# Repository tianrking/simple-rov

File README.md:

<div align="center">

# SimpleROV

**A compact four-thruster underwater robot.**

Printable mechanics · Documented assembly · MuJoCo simulation

[**English**](README.md) · [Español](README.es.md) · [简体中文](README.zh-CN.md)

**213 × 210 × 148 mm** &nbsp; · &nbsp; **4 thrusters** &nbsp; · &nbsp; **10 printed parts**

[Assembly guide](docs/assembly.md) · [Download](https://github.com/tianrking/simple-rov/releases) · [CAD files](mechanical/README.md) · [Simulation](docs/simulation.md) · [Gallery](docs/gallery.md)

</div>

SimpleROV brings the frame, thruster mounts, camera carrier, enclosure mounts and simulation into one reproducible project. Start with a mechanical fit check, then develop tethered remote control, depth hold and heading hold around the same coordinate system.

The **standard assembly has no top buoyancy foam or retention straps**. Mounting routes remain available for an optional buoyancy module, selected after measuring the completed vehicle's mass and trim. These images are CAD renderings, not photographs of tested hardware.

## Simulation videos

**Watch the 48-second overview directly below:** four actual MuJoCo scenarios, 720p H.264, live telemetry and the forward camera.

https://github.com/user-attachments/assets/2bf94293-84e5-456a-9249-f08cb007cc9f

| Chapter | Overview time | What to watch | Individual video |
|---|---|---|---|
| Basic motion | 00:00-00:12 | Rise, descend, move forward and turn | [Pool](docs/assets/videos/pool.mp4) |
| Water current | 00:12-00:24 | Current arrow, changing position and lateral drift | [Cross-current](docs/assets/videos/cross-current.mp4) |
| Tether load | 00:24-00:36 | Tension/slack state and line force at the chassis eye | [Tether](docs/assets/videos/tethered.mp4) |
| Motor failure | 00:36-00:48 | H_LEFT at zero thrust, rank loss and allocation residual | [Motor fault](docs/assets/videos/motor-fault.mp4) |

[All video players and reproduction details](docs/videos.md) · [Download the overview MP4](docs/assets/videos/simple-rov-overview.mp4)

<details>
<summary><strong>Animated preview for mirrors without native video playback</strong></summary>

</details>

These are simulated trajectories with uncalibrated parameters, sensor feedback and seed 0. They are classical-control demonstrations, not physical robot footage. MP4 originals, per-frame state traces and exact run metadata are committed alongside the rendering source.

## At a glance

| Mechanics | Propulsion | Development |
|---|---|---|
| Compact load-bearing frame | Two horizontal + two vertical thrusters | Editable CadQuery source and STEP |
| Commercial central dry enclosure | Forward/reverse, ascent/descent, yaw | Independent, bed-oriented STL files |
| Removable fairing and skids | Differential vertical thrust assists roll | MuJoCo environment and classical control |
| Optional top buoyancy module | Four independent force commands | Illustrated assembly, BOM and checks |

| Specification | Current reference |
|---|---|
| Standard envelope, L × W × H | **213 × 210 × 148 mm** |
| With the reference buoyancy module | 213 × 210 × 184.7 mm |
| Main printed parts | 10, plus 2 separate motor-fit coupons |
| Thruster reference | 4 × APISQUEEN X2 complete waterproof thrusters |
| Central enclosure reference | Blue Robotics 50 mm series, 150 mm tube, 58 mm outside diameter |
| Camera reference | Blue Robotics Low-Light HD USB Camera |
| Coordinates | X forward, Y left, Z up; CAD in mm, simulation in m |

Dimensions exclude the final cables, penetrators, tether termination, strap buckles and ballast. Sway and pitch have no independent actuators. Actual motor threads, cable exits and the complete electrical packaging still need physical confirmation.

## Explore the structure

| Inside the frame | Optional buoyancy module |
|:---:|:---:|
|  |  |

The interior view removes the fairing and pressure enclosure components to show the camera carrier, tray and mounts. It does not imply that the final battery, controller, four ESCs and video host have been packaged.

<details>
<summary><strong>Open the six individual views</strong></summary>

| Front | Rear |
|:---:|:---:|
|  |  |

| Left | Right |
|:---:|:---:|
|  |  |

| Top | Bottom |
|:---:|:---:|
|  |  |

</details>

### In Onshape

These are **actual screenshots of the historical cloud assembly**, shown with the optional foam and straps fitted. The repository's standard STEP remains the reference for the default, foam-free configuration.

| Assembly workspace | Profile detail |
|:---:|:---:|
|  |  |

[Open the public Onshape assembly](https://cad.onshape.com/documents/256f9be06adfdc472f7aac06/w/aefb43ce726d3d5c24877f23/e/1186baa4f5bb2c01f6be971a) · [View provenance and import limitations](docs/gallery.md#onshape-screenshots)

## What each part does

| Part | Qty. | Purpose |
|---|---:|---|
| Load chassis | 1 | Carries thrust loads and joins the skids, enclosure, mounts and fairing; provides tether and ballast interfaces |
| Upper fairing | 1 | Protects the structure and defines its outline; freely floods and is not a pressure vessel |
| Skids | 2 | Support the vehicle on a bench or pool floor and protect its underside |
| Enclosure clamps | 2 | Retain the commercial tube with soft liners; do not seal the endcaps |
| Vertical carriers | 2 | Mount the vertical thrusters and transfer their loads to the chassis |
| Internal tray | 1 | Supports the camera carrier and future electronics adapters; positive axial retention remains to be designed |
| Camera carrier | 1 | Positions the camera board and provides lens, USB and fastener clearance |
| Commercial pressure enclosure | 1 set | Keeps ordinary electronics dry when correctly assembled and leak-tested |
| Commercial thrusters | 4 | Complete motor, propeller and duct assemblies; not printed by this project |
| Buoyancy foam and straps | Optional | Add buoyancy and adjust trim after measurement |

## Choose an assembly

| Configuration | Top foam / straps | Assembly STEP | With nominal metal fasteners |
|---|---|---|---|
| **Standard** `base` | None | [simple-rov.step](mechanical/assemblies/simple-rov.step) | [Fastener assembly](mechanical/assemblies/simple-rov-with-fasteners.step) |
| Optional `with-buoyancy` | 2 foam pieces / 4 straps | [Buoyancy assembly](mechanical/assemblies/simple-rov-with-buoyancy.step) | [Buoyancy + fasteners](mechanical/assemblies/simple-rov-buoyancy-with-fasteners.step) |

Both configurations share the same ten printed parts. Foam is cut from suitable closed-cell material; it is **not printed as part of the fairing**. Its default purchase quantity is zero, with optional quantities recorded separately.

Omitting foam does not establish positive buoyancy or guarantee a passive ascent. Weigh the complete vehicle, measure displacement and check fully submerged trim before deciding whether to add foam or ballast. See [buoyancy and trim](docs/buoyancy.md).

## Build a first prototype

1. **Check one motor first.** Buy one reference thruster and a matching bidirectional ESC. Test both [fit coupons](mechanical/fit_coupons/) against the actual mounting face, holes, blind depth and cable exit.
2. **Check the dry payload.** Lay out the real battery, four ESCs, controller, video host, connectors and wiring at full scale before assuming they fit the tube.
3. **Print and assemble.** Use the [print manifest](bom/PRINT_MANIFEST.csv), [fastener BOM](bom/BOM_FASTENERS.csv) and [illustrated guide](docs/assembly.md). Install skids before horizontal thrusters obstruct their tool paths.
4. **Complete retention and wiring.** Add board-specific insulated adapters and positive tray retention. Select penetrators for the actual cable construction.
5. **Leak-test and trim.** Test the complete empty enclosure, then use representative payload mass to establish buoyancy and balance.
6. **Run controlled shallow-water checks.** Verify individual thrust directions, remote commands, depth/heading hold and loss-of-command shutdown in a recoverable setting.

The guide specifies screw directions, washers, quantities and inspection hold points. Start with [assembly](docs/assembly.md), [acceptance](docs/acceptance.md) and the [prototype build plan](docs/build-plan.md).

## Run the simulation

From the repository root, using Python 3.12:

```bash
git clone https://github.com/tianrking/simple-rov.git
cd simple-rov
python3 -m venv .venv
source .venv/bin/activate
python -m pip install -r requirements/sim.txt
python simulation/mujoco/run.py --viewer --manual --seconds 300
```

On Windows, activate with `.venv\Scripts\activate`. On macOS, after installing dependencies, you can also open `launch-macos.command`.

| Control | Input |
|---|---|
| Forward / reverse | Hold W / S; release to cancel surge thrust |
| Turn left / right | A / D; change heading target by 15° |
| Ascend / descend | U / J; change depth target by 0.1 m |
| Hold current depth and heading | X; does not lock horizontal position |
| Orbit / zoom | Left mouse drag / scroll wheel |
| Quit | Esc or close the window |

The dedicated driving window isolates these keys from MuJoCo's built-in viewer shortcuts. Losing focus cancels surge thrust; the vehicle can still coast.

```bash
# Display the optional assembly
python simulation/mujoco/run.py --viewer --manual --configuration with-buoyancy --seconds 300

# Record an automatic demonstration, state CSV and camera views
python simulation/mujoco/run.py --render --output-dir runs/demo
```

### Physics and control

Powered by **MuJoCo 4.0.1**, the foundation includes relative-current drag, buoyancy, delayed/rate-limited actuators, bounded allocation, sensor proxies, classical control, a lumped tether and fault scenarios. [Simulation foundation](docs/simulation-foundation.md). **Mass, inertia, centers of gravity/buoyancy, displacement, drag and reverse thrust are uncalibrated example parameters.** Changing the assembly changes visuals and associated collision proxies; it does not automatically recalculate those parameters.

This is a fully submerged, still-water model. It includes configurable current and a tension-only tether approximation; it does not include waves, free-surface transitions, distributed cable dynamics, CFD or realistic underwater optics. Open it through `run.py`: loading an XML alone omits the Python underwater forces.

```python
from simulation.mujoco.environment import ROV

rov = ROV(configuration="base")
for _ in range(1000):
    forces = rov.controller(depth=1.2, surge_N=2.0, yaw=0.0)
    position, attitude, velocity, angular_velocity = rov.step(forces)
```

Commands are forces in newtons, ordered horizontal-left, horizontal-right, vertical-left, vertical-right. They are not PWM or RPM. Keyboard commands set surge thrust, target depth and target heading; classical feedback stabilizes depth, roll and heading. [Driving and control documentation](docs/simulation.md).

To try a water current while driving:

```bash
python simulation/mujoco/run.py --scenario cross-current --viewer --manual --seconds 300
```

The development path is **mechanical fit and assembly → tethered remote operation → classical stabilization → measured calibration and shallow-water trials**. Custom PCB work is deferred; the current release focuses on mechanics, assembly and remote-control simulation.

## Edit and reproduce

| Need | Entry point |
|---|---|
| Ten bed-oriented prints | [mechanical/stl/](mechanical/stl/) |
| Ten editable STEP parts | [mechanical/step_parts/](mechanical/step_parts/) |
| Dimensions and CAD source | [parameters.json](mechanical/parameters.json) · [build.py](mechanical/build.py) |
| Configuration inventory | [configurations.json](mechanical/configurations.json) |
| Printed, purchased and metal parts | [bom/](bom/) |
| Installation instructions | [Assembly guide](docs/assembly.md) · [PDF](docs/assembly.pdf) |
| Change workflow and checks | [Development guide](docs/development.md) |

<details>
<summary><strong>CAD and simulation rebuild commands</strong></summary>

```bash
python -m pip install -r requirements/cad.txt
python mechanical/build.py
python mechanical/build_fit_coupons.py
python mechanical/verify.py
python mechanical/export_metadata.py
python mechanical/verify_configurations.py
python simulation/mujoco/build_model.py
python simulation/mujoco/verify.py
python simulation/mujoco/verify_manual.py
```

</details>

When changing motors, check the full envelope, mounting-face offset, hole pattern, depth, cable exit, propeller flow paths and screw length. Keep CAD, BOM, documents and simulation in sync. Existing part IDs are retained for compatibility with printed parts and hole tables.

```text
mechanical/          Parametric CAD, separate parts, assemblies and supplier references
simulation/mujoco/   Underwater forces, classical control, driving and checks
bom/                 Print, purchase, fastener and interface records
electronics/         Future KiCad work and mechanical interface constraints
firmware/            Future onboard implementation and failure handling
docs/                Assembly, design, trim, simulation, development and images
validation/          Digital check records and historical Onshape import records
requirements/        Dependencies grouped by purpose
runs/                Local outputs; excluded from version control
```

## Project status

| Available now | Still to validate or develop |
|---|---|
| Parametric mechanics, separate prints and two assembly variants | Actual motor mounting depth, cable exits and print load capacity |
| Illustrated guide, mechanical BOM and hole coordinates | Full electronics packaging, tray retention, penetrators and thermal management |
| MuJoCo demonstrator and classical control | Measured mass, trim, thrust and hydrodynamic calibration |
| Digital consistency and regression checks | Physical assembly, sealing and shallow-water trials |

PCB manufacturing files and flashable firmware are future work. Digital checks are evidence about files, geometry and software, not a reliability or depth certification. [Status](STATUS.json) · [Roadmap](docs/roadmap.md) · [Changelog](CHANGELOG.md).

## Rights and sources

This repository is public for review. **All rights reserved for original content; no open-source license is granted.** Third-party CAD, manufacturer drawings and dependencies retain their owners' rights. [License](LICENSE) · [Third-party notices](THIRD_PARTY_NOTICES.md) · [Sources](SOURCES.json).

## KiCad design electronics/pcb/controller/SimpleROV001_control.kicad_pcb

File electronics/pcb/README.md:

# SimpleROV v0.0.1 hardware

Frozen engineering controller PCB for the current80x32mm interface. Native KiCad10 sources, checked reports, procurement/assembly files and mechanical exports are provided. This is a prototype design ready for independent fabrication review, not a tested propulsion system.

- Open controller/SimpleROV001_control.kicad_pro. Its local symbol library, used standard footprint subsets, modified footprint library and STEP models are included.
- verification/ERC.json and DRC.json are untouched KiCad CLI reports. DRC has0violations/0unconnected/0schematic-parity issues with no ignored DRC checks or exclusions. ERC has0violations; only SPICE model checking is ignored, because no SPICE simulation is claimed.
- controller/source/netlist.xml is exported from the final schematic. docs/CONNECTOR_PINOUT.csv and controller/source/physical_placement.json follow the final native PCB, not the earlier proposal.
- controller/BOM.csv lists individual purchased parts; controller/manufacturing holds fabrication layers, separate drills and SMT-only placement data. USB is a manual mixed-technology placement.
- mechanical/controller_assembled.step uses board-bottom origin and includes111 KiCad model instances plus explicit IMU/USB envelopes. Mated connector keepouts and wire-bend reservations are separate STEP files, built from final native placement. Apply world translation[-50,-16,13]mm to each. Complete enclosure and cable fit is still a system integration task.
- docs/FAULT_CHAIN_AND_SENSE.md gives J9 arming behavior, non-inverting PWM and the1k0.5W source-resistor MPN/formula. docs/DESIGN_AND_QUALIFICATION.md specifies assembly and the unperformed physical qualification stages.
- controller/source/rebuild.py reproduces a separate candidate from frozen JSON, local libraries and the saved route session. It reruns ERC/DRC. See controller/source/REPRODUCE.md.

The prototype requires the exact5V-BEC ESC interface. Inhibit is static HIGH/no frames and does not prove the motor stops. First system commissioning is limited to regulated12V/5A total, per the main system plan. No board firmware or physical bench tests are represented as completed.

Original SimpleROV project materials:All rights reserved. Redistributed KiCad collections and modified KiCad footprints remain under the upstream CC BY-SA4.0 license with its electronic-design exception; see controller/third_party. No vendor datasheet full texts are redistributed. This package does not write, commit or push the shared repository.

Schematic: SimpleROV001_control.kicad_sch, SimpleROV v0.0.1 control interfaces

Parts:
C1, C2: 4.7u 10V; C_0805_2012Metric; MPN GRM21BR71A475KA73L
C3, C19, C21, C22, C23, C24, C25, C26, C27, C28, C29, C32: 100n 16V; C_0603_1608Metric; MPN GRM188R71C104KA01D
C4, C14: 1u 16V; C_0603_1608Metric; MPN GRM188R71C105KA12D
C5, C18: 2.2u 10V; C_0603_1608Metric; MPN GRM188R71A225KE15D
C6, C7, C8, C9, C10, C11, C12, C13, C15: 100n 16V; C_0402_1005Metric; MPN GRM155R71C104KA88D
C16, C17: 15p 50V C0G; C_0603_1608Metric; MPN GRM1885C1H150JA01D
C20, C30, C31: 10n 50V; C_0603_1608Metric; MPN GRM188R71H103KA01D
D1: SS14; D_SMA; MPN SS14-E3/61T
D2: SS14; D_SMA_SilkTrim; MPN SS14-E3/61T
D3: USBLC6-2SC6; SOT-23-6; MPN USBLC6-2SC6
D4: BAT54S,215; SOT-23; MPN BAT54S,215
D5: STATUS GREEN; LED_0603_1608Metric; MPN LTST-C190KGKT
F1: 500mA 32V FAST; Fuse_1206_3216Metric; MPN 0467.500NR
J1: J1 SYS5V / GND; JST_GH_BM02B-GHS-TBT_1x02-1MP_P1.25mm_Vertical; MPN BM02B-GHS-TBT(LF)(SN)
J2: J2 GND / UART_TX_PORT / UART_RX_PORT; JST_GH_BM03B-GHS-TBT_1x03-1MP_P1.25mm_Vertical; MPN BM03B-GHS-TBT(LF)(SN)
J3: J3 ESC_HL_5V / ESC_HL_PWM_PORT / ESC_HL_GND; JST_GH_BM03B-GHS-TBT_1x03-1MP_P1.25mm_Vertical; MPN BM03B-GHS-TBT(LF)(SN)
J4: J4 ESC_HR_5V / ESC_HR_PWM_PORT / ESC_HR_GND; JST_GH_BM03B-GHS-TBT_1x03-1MP_P1.25mm_Vertical; MPN BM03B-GHS-TBT(LF)(SN)
J5: J5 ESC_VL_5V / ESC_VL_PWM_PORT / ESC_VL_GND; JST_GH_BM03B-GHS-TBT_1x03-1MP_P1.25mm_Vertical; MPN BM03B-GHS-TBT(LF)(SN)
J6: J6 ESC_VR_5V / ESC_VR_PWM_PORT / ESC_VR_GND; JST_GH_BM03B-GHS-TBT_1x03-1MP_P1.25mm_Vertical; MPN BM03B-GHS-TBT(LF)(SN)
J7: J7 DEPTH_3V3 / DEPTH_SCL / DEPTH_SDA / GND; JST_GH_BM04B-GHS-TBT_1x04-1MP_P1.25mm_Vertical; MPN BM04B-GHS-TBT(LF)(SN)
J8: J8 LEAK_LIMIT / LEAK_RETURN; JST_GH_BM02B-GHS-TBT_1x02-1MP_P1.25mm_Vertical; MPN BM02B-GHS-TBT(LF)(SN)
J9: J9 V3V3 / ARM_KEY; JST_GH_BM02B-GHS-TBT_1x02-1MP_P1.25mm_Vertical; MPN BM02B-GHS-TBT(LF)(SN)
J10: BATTERY SENSE + ONLY; TestPoint_Pad_D2.0mm; MPN BATTERY SENSE + ONLY
J11: USB SERVICE ONLY; USB_MicroB_Molex105017_SilkTrim; MPN 1050170001
R1, R4, R9, R14, R44, R48: 1k; R_0603_1608Metric; MPN RC0603FR-071KL
R2, R34, R35: 33; R_0603_1608Metric; MPN RC0603FR-0733RL
R3, R5, R15, R26, R27, R28, R29, R45: 10k; R_0603_1608Metric; MPN RC0603FR-0710KL
R6, R7: 27; R_0603_1608Metric; MPN RC0603FR-0727RL
R8, R38: 10; R_0603_1608Metric; MPN RC0603FR-0710RL
R10, R12, R13, R16, R17, R22, R23, R24, R25, R39: 100k; R_0603_1608Metric; MPN RC0603FR-07100KL
R11: 2.2k; R_0603_1608Metric; MPN RC0603FR-072K2L
R18, R19, R20, R21: 365; R_0603_1608Metric; MPN RC0603FR-07365RL
R30, R31, R32, R33, R46, R47: 100; R_0603_1608Metric; MPN RC0603FR-07100RL
R36, R37: 4.7k; R_0603_1608Metric; MPN RC0603FR-074K7L
R40, R41: 3.3k; R_0603_1608Metric; MPN RC0603FR-073K3L
R42: 147k 0.1%; R_0603_1608Metric; MPN RT0603BRD07147KL
R43: 27k 0.1%; R_0603_1608Metric; MPN RT0603BRD0727KL
R49: 330; R_0603_1608Metric; MPN RC0603FR-07330RL
SW1: BOOTSEL; SW_SPST_B3U-1000P; MPN B3U-1000P
SW2: RESET; SW_SPST_B3U-1000P; MPN B3U-1000P
TP1: SWDIO; TestPoint_Pad_D1.0mm; MPN SWDIO
TP2: SWCLK; TestPoint_Pad_D1.0mm; MPN SWCLK
TP3: GND; TestPoint_Pad_D1.0mm; MPN GND
TP4: V3V3; TestPoint_Pad_D1.0mm; MPN V3V3
TP5: RUN; TestPoint_Pad_D1.0mm; MPN RUN
TP6: ARM_LATCH_Q; TestPoint_Pad_D1.0mm; MPN ARM_LATCH_Q
U1: RP2040; QFN-56-1EP_7x7mm_P0.4mm_EP3.2x3.2mm; MPN RP2040
U2: TLV75533PDBVR; SOT-23-5; MPN TLV75533PDBVR
U3: ICM-42688-P; LGA-14_3x2.5mm_P0.5mm_LayoutBorder3x4y; MPN ICM-42688-P
U4: W25Q16JVSNIQ; SOIC-8_3.9x4.9mm_P1.27mm; MPN W25Q16JVSNIQ
U5, U6, U7, U8: TLP2361(TPL,E; SO-5-6_4.55x3.7mm_P1.27mm; MPN TLP2361(TPL,E
U9: STWD100NXWY3F; SOT-23-5; MPN STWD100NXWY3F
U10: SN74LVC1G11DCKR; SOT-363_SC-70-6; MPN SN74LVC1G11DCKR
U11: SN74LVC126APWR; TSSOP-14_4.4x5mm_P0.65mm; MPN SN74LVC126APWR
U12: SN74HCS74PWR; TSSOP-14_4.4x5mm_P0.65mm; MPN SN74HCS74PWR
U13: SN74LVC1G97DCKR; SOT-363_SC-70-6; MPN SN74LVC1G97DCKR
Y1: 12MHz CL10p; Crystal_SMD_3225-4Pin_3.2x2.5mm; MPN ABM8-272-T3

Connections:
/ARM_CLEAR_DRIVE: R14.1, U13.4 (Y)
/ARM_CLR: R48.2, U12.1 (CLR1)
/ARM_CLR_RC: C21.1, R13.2, R14.2, R48.1
/ARM_FEED: J9.1 (3V3_ARM_FEED), R49.2
/ARM_KEY: J9.2 (ARM_KEY), R11.1, U1.15 (GPIO12), U10.1 (A), U13.6 (In2)
/ARM_LATCH_Q: TP6.1, U1.18 (GPIO15), U10.3 (B), U12.5 (Q1)
/ARM_SET: R12.1, U1.34 (GPIO22), U12.3 (CLK1)
/AVDD: C14.1, C15.1, R8.2, U1.43 (ADC_AVDD)
/BOOT_BTN: R4.2, SW1.1
/DEPTH_3V3: J7.1 (DEPTH_3V3), R38.2
/DEPTH_SCL: J7.2 (DEPTH_SCL), R34.2, R36.2
/DEPTH_SCL_MCU: R34.1, U1.7 (GPIO5)
/DEPTH_SDA: J7.3 (DEPTH_SDA), R35.2, R37.2
/DEPTH_SDA_MCU: R35.1, U1.6 (GPIO4)
/ESC_HL_5V: C26.1, J3.1 (ESC_HL_5V), U5.6 (VDD)
/ESC_HL_GND: C26.2, J3.3 (ESC_HL_GND), U5.4 (GND)
/ESC_HL_PWM: R30.1, U5.5 (VO)
/ESC_HL_PWM_PORT: J3.2 (ESC_HL_PWM_PORT), R30.2
/ESC_HR_5V: C27.1, J4.1 (ESC_HR_5V), U6.6 (VDD)
/ESC_HR_GND: C27.2, J4.3 (ESC_HR_GND), U6.4 (GND)
/ESC_HR_PWM: R31.1, U6.5 (VO)
/ESC_HR_PWM_PORT: J4.2 (ESC_HR_PWM_PORT), R31.2
/ESC_VL_5V: C28.1, J5.1 (ESC_VL_5V), U7.6 (VDD)
/ESC_VL_GND: C28.2, J5.3 (ESC_VL_GND), U7.4 (GND)
/ESC_VL_PWM: R32.1, U7.5 (VO)
/ESC_VL_PWM_PORT: J5.2 (ESC_VL_PWM_PORT), R32.2
/ESC_VR_5V: C29.1, J6.1 (ESC_VR_5V), U8.6 (VDD)
/ESC_VR_GND: C29.2, J6.3 (ESC_VR_GND), U8.4 (GND)
/ESC_VR_PWM: R33.1, U8.5 (VO)
/ESC_VR_PWM_PORT: J6.2 (ESC_VR_PWM_PORT), R33.2
/FLASH_CS: R3.2, R4.1, U1.56 (~QSPI_SS), U4.1 (CS)
/GND: C1.2, C2.2, C3.2, C4.2, C5.2, C6.2, C7.2, C8.2, C9.2, C10.2, C11.2, C12.2, C13.2, C14.2, C15.2, C16.2, C17.2, C18.2, C19.2, C20.2, C21.2, C22.2, C23.2, C24.2, C25.2, C30.2, C31.2, C32.2, D3.2 (GND), D4.1 (A1), D5.1 (K), J1.2 (GND), J2.1 (GND), J7.4 (GND), J11.5 (GND), J11.SH (SHIELD), R10.2, R11.2, R12.2, R13.1, R16.2, R17.2, R22.2, R23.2, R24.2, R25.2, R41.2, R43.2, R45.2, SW1.2, SW2.2, TP3.1, U1.19 (TESTEN), U1.57 (GND), U2.2 (GND), U3.2 (RESV), U3.3 (RESV), U3.6 (GND), U3.7 (RESV_GND), U3.9 (INT2_FSYNC), U3.10 (RESV), U3.11 (RESV), U4.4 (GND), U9.2 (GND), U9.3 (EN), U10.2 (GND), U11.7 (GND), U12.7 (GND), U12.11 (CLK2), U12.12 (D2), U12.13 (CLR2), U13.1 (In1), U13.2 (GND), Y1.2 (GND), Y1.4 (GND)
/IMU_CS: U1.28 (GPIO17), U3.12 (AP_CS)
/IMU_INT: U1.31 (GPIO20), U3.4 (INT1)
/IMU_MISO: U1.27 (GPIO16), U3.1 (AP_SDO)
/IMU_MOSI: U1.30 (GPIO19), U3.14 (AP_SDI)
/IMU_SCK: U1.29 (GPIO18), U3.13 (AP_SCLK)
/LEAK_ADC: C31.1, R39.2, R40.1, U1.39 (GPIO27/ADC1)
/LEAK_LIMIT: J8.1 (LEAK_LIMIT), R40.2
/LEAK_RETURN: J8.2 (LEAK_RETURN), R41.1
/LED_HL: R18.2, U5.1 (A)
/LED_HR: R19.2, U6.1 (A)
/LED_STATUS_A: D5.2 (A), R9.2
/LED_VL: R20.2, U7.1 (A)
/LED_VR: R21.2, U8.1 (A)
/MCU_ENABLE: R10.1, U1.14 (GPIO11), U10.6 (C)
/OUTPUT_ENABLE: R17.1, U10.4 (Y), U11.1 (OE1), U11.4 (OE2), U11.10 (OE3), U11.13 (OE4)
/PWM_HL_BUF: R26.1, U5.3 (K), U11.3 (Y1)
/PWM_HL_RAW: R22.1, U1.8 (GPIO6), U11.2 (A1)
/PWM_HR_BUF: R27.1, U6.3 (K), U11.6 (Y2)
/PWM_HR_RAW: R23.1, U1.9 (GPIO7), U11.5 (A2)
/PWM_VL_BUF: R28.1, U7.3 (K), U11.8 (Y3)
/PWM_VL_RAW: R24.1, U1.11 (GPIO8), U11.9 (A3)
/PWM_VR_BUF: R29.1, U8.3 (K), U11.11 (Y4)
/PWM_VR_RAW: R25.1, U1.12 (GPIO9), U11.12 (A4)
/QSPI_IO0: U1.53 (QSPI_SD0), U4.5 (DI_IO0)
/QSPI_IO1: U1.55 (QSPI_SD1), U4.2 (DO_IO1)
/QSPI_IO2: U1.54 (QSPI_SD2), U4.3 (WP_IO2)
/QSPI_IO3: U1.51 (QSPI_SD3), U4.7 (HOLD_IO3)
/QSPI_SCLK: R2.2, U4.6 (CLK)
/QSPI_SCLK_MCU: R2.1, U1.52 (QSPI_SCLK)
/RUN: R5.2, SW2.1, TP5.1, U1.26 (RUN)
/STATUS_LED: R9.1, U1.17 (GPIO14)
/SWCLK: TP2.1, U1.24 (SWCLK)
/SWDIO: TP1.1, U1.25 (SWDIO)
/SYS5V: F1.1, J1.1 (SYS5V)
/SYS5V_FUSED: D1.2 (A), F1.2
/UART_RX: R47.2, U1.3 (GPIO1)
/UART_RX_PORT: J2.3 (UART_RX_PORT), R47.1
/UART_TX: R46.1, U1.2 (GPIO0)
/UART_TX_PORT: J2.2 (UART_TX_PORT), R46.2
/USB_DM: D3.3 (IO2), D3.4 (IO2), J11.2 (D-), R6.2
/USB_DM_MCU: R6.1, U1.46 (USB_DM)
/USB_DP: D3.1 (IO1), D3.6 (IO1), J11.3 (D+), R7.2
/USB_DP_MCU: R7.1, U1.47 (USB_DP)
/USB_VBUS: D2.2 (A), D3.5 (VBUS), J11.1 (VBUS)
/V1V1: C5.1, C12.1, C13.1, U1.23 (DVDD), U1.45 (VREG_VOUT), U1.50 (DVDD)
/V3V3: C1.1, C3.1, C4.1, C6.1, C7.1, C8.1, C9.1, C10.1, C11.1, C18.1, C19.1, C20.1, C22.1, C23.1, C24.1, C25.1, C32.1, D4.2 (K2), R3.1, R5.1, R8.1, R15.1, R18.1, R19.1, R20.1, R21.1, R26.2, R27.2, R28.2, R29.2, R36.1, R37.1, R38.1, R39.1, R45.1, R49.1, TP4.1, U1.1 (IOVDD), U1.10 (IOVDD), U1.22 (IOVDD), U1.33 (IOVDD), U1.42 (IOVDD), U1.44 (VREG_VIN), U1.48 (USB_VDD), U1.49 (IOVDD), U2.5 (OUT), U3.5 (VDDIO), U3.8 (VDD), U4.8 (VCC), U9.5 (VCC), U10.5 (VCC), U11.14 (VCC), U12.2 (D1), U12.4 (PRE1), U12.10 (PRE2), U12.14 (VCC), U13.5 (VCC)
/V5_BOARD: C2.1, D1.1 (K), D2.1 (K), U2.1 (IN), U2.3 (EN)
/VBAT_ADC: D4.3 (K1_A2), R44.2, U1.38 (GPIO26/ADC0)
/VBAT_DIV: C30.1, R42.2, R43.1, R44.1
/VBAT_IN: J10.1, R42.1
/WDI: R16.1, U1.13 (GPIO10), U9.4 (WDI)
/WDT_OK: R15.2, U1.16 (GPIO13), U9.1 (WDO), U13.3 (In0)
/XIN: C16.1, U1.20 (XIN), Y1.1
/XOUT: R1.1, U1.21 (XOUT)
/XTAL_OUT: C17.1, R1.2, Y1.3

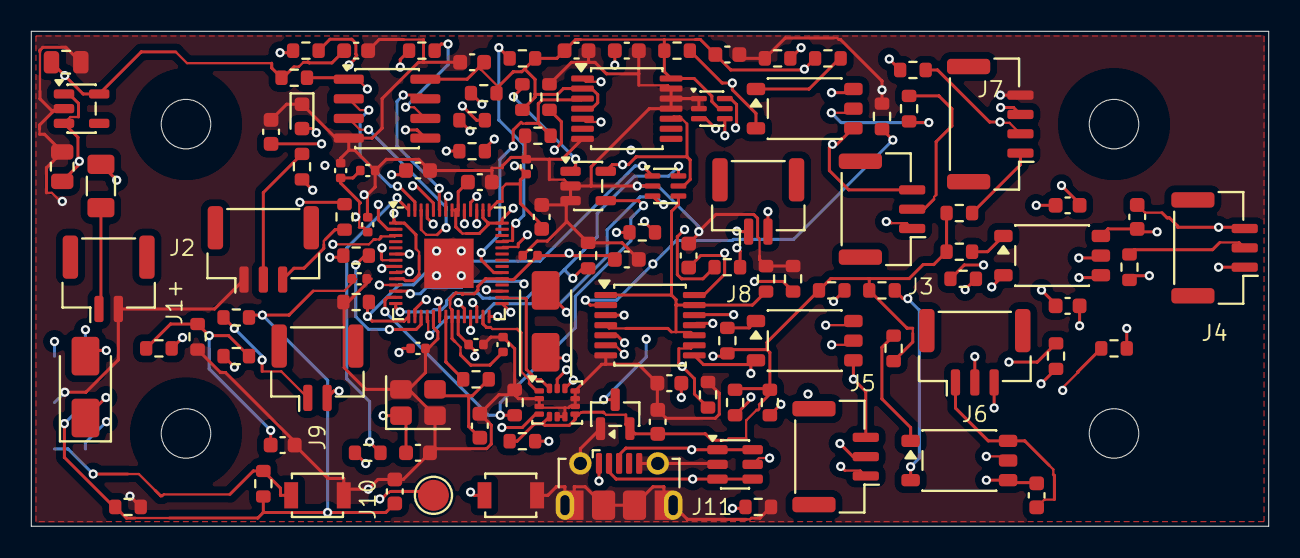
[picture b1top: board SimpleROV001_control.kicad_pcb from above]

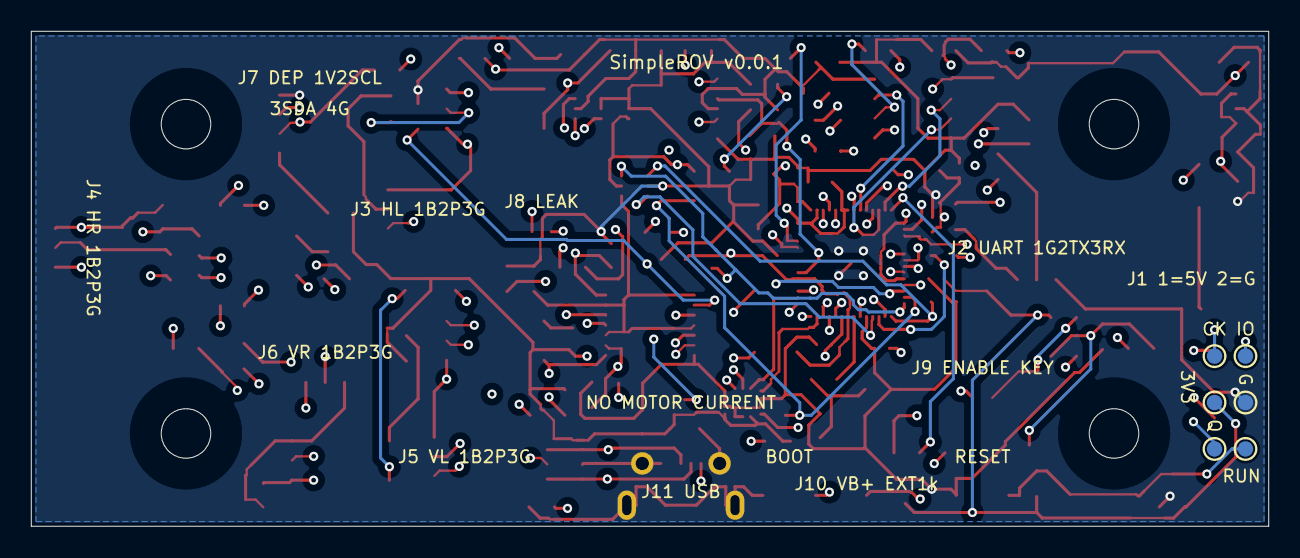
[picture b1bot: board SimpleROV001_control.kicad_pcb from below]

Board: 4 copper layers, 80.0 x 32.0 mm, 124 parts (6 on the bottom side), 87 nets.

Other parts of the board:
H1, H2, H3, H4: MountingHole_3.2mm_M3; MountingHole3.2_M3_Clearance

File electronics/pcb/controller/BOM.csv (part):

Reference,Value,MPN,Footprint,Datasheet,Qty
U1,RP2040,RP2040,Package_DFN_QFN:QFN-56-1EP_7x7mm_P0.4mm_EP3.2x3.2mm,https://datasheets.raspberrypi.com/rp2040/rp2040-datasheet.pdf,1
U2,TLV75533PDBVR,TLV75533PDBVR,Package_TO_SOT_SMD:SOT-23-5,https://www.ti.com/lit/ds/symlink/tlv755p.pdf,1
U3,ICM-42688-P,ICM-42688-P,Package_LGA:LGA-14_3x2.5mm_P0.5mm_LayoutBorder3x4y,https://product.tdk.com/system/files/dam/doc/product/sensor/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,1
U4,W25Q16JVSNIQ,W25Q16JVSNIQ,Package_SO:SOIC-8_3.9x4.9mm_P1.27mm,https://www.winbond.com/resource-files/W25Q16JV%20RevH%20041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,1
U5,"TLP2361(TPL,E","TLP2361(TPL,E",Package_SO:SO-5-6_4.55x3.7mm_P1.27mm,https://toshiba.semicon-storage.com/info/TLP2361_datasheet_e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,1
U6,"TLP2361(TPL,E","TLP2361(TPL,E",Package_SO:SO-5-6_4.55x3.7mm_P1.27mm,https://toshiba.semicon-storage.com/info/TLP2361_datasheet_e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,1
U7,"TLP2361(TPL,E","TLP2361(TPL,E",Package_SO:SO-5-6_4.55x3.7mm_P1.27mm,https://toshiba.semicon-storage.com/info/TLP2361_datasheet_e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,1
U8,"TLP2361(TPL,E","TLP2361(TPL,E",Package_SO:SO-5-6_4.55x3.7mm_P1.27mm,https://toshiba.semicon-storage.com/info/TLP2361_datasheet_e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,1
U9,STWD100NXWY3F,STWD100NXWY3F,Package_TO_SOT_SMD:SOT-23-5,https://www.st.com/resource/en/datasheet/stwd100.pdf,1
U10,SN74LVC1G11DCKR,SN74LVC1G11DCKR,Package_TO_SOT_SMD:SOT-363_SC-70-6,https://www.ti.com/lit/ds/symlink/sn74lvc1g11.pdf,1
U11,SN74LVC126APWR,SN74LVC126APWR,Package_SO:TSSOP-14_4.4x5mm_P0.65mm,https://www.ti.com/lit/ds/symlink/sn74lvc126a.pdf,1
U12,SN74HCS74PWR,SN74HCS74PWR,Package_SO:TSSOP-14_4.4x5mm_P0.65mm,https://www.ti.com/lit/ds/symlink/sn74hcs74.pdf,1
J1,J1 SYS5V / GND,BM02B-GHS-TBT(LF)(SN),Connector_JST:JST_GH_BM02B-GHS-TBT_1x02-1MP_P1.25mm_Vertical,https://www.jst-mfg.com/product/index.php?series=105,1
J2,J2 GND / UART_TX_PORT / UART_RX_PORT,BM03B-GHS-TBT(LF)(SN),Connector_JST:JST_GH_BM03B-GHS-TBT_1x03-1MP_P1.25mm_Vertical,https://www.jst-mfg.com/product/index.php?series=105,1
J3,J3 ESC_HL_5V / ESC_HL_PWM_PORT / ESC_HL_GND,BM03B-GHS-TBT(LF)(SN),Connector_JST:JST_GH_BM03B-GHS-TBT_1x03-1MP_P1.25mm_Vertical,https://www.jst-mfg.com/product/index.php?series=105,1
J4,J4 ESC_HR_5V / ESC_HR_PWM_PORT / ESC_HR_GND,BM03B-GHS-TBT(LF)(SN),Connector_JST:JST_GH_BM03B-GHS-TBT_1x03-1MP_P1.25mm_Vertical,https://www.jst-mfg.com/product/index.php?series=105,1
J5,J5 ESC_VL_5V / ESC_VL_PWM_PORT / ESC_VL_GND,BM03B-GHS-TBT(LF)(SN),Connector_JST:JST_GH_BM03B-GHS-TBT_1x03-1MP_P1.25mm_Vertical,https://www.jst-mfg.com/product/index.php?series=105,1
J6,J6 ESC_VR_5V / ESC_VR_PWM_PORT / ESC_VR_GND,BM03B-GHS-TBT(LF)(SN),Connector_JST:JST_GH_BM03B-GHS-TBT_1x03-1MP_P1.25mm_Vertical,https://www.jst-mfg.com/product/index.php?series=105,1
J7,J7 DEPTH_3V3 / DEPTH_SCL / DEPTH_SDA / GND,BM04B-GHS-TBT(LF)(SN),Connector_JST:JST_GH_BM04B-GHS-TBT_1x04-1MP_P1.25mm_Vertical,https://www.jst-mfg.com/product/index.php?series=105,1
J8,J8 LEAK_LIMIT / LEAK_RETURN,BM02B-GHS-TBT(LF)(SN),Connector_JST:JST_GH_BM02B-GHS-TBT_1x02-1MP_P1.25mm_Vertical,https://www.jst-mfg.com/product/index.php?series=105,1
J9,J9 V3V3 / ARM_KEY,BM02B-GHS-TBT(LF)(SN),Connector_JST:JST_GH_BM02B-GHS-TBT_1x02-1MP_P1.25mm_Vertical,https://www.jst-mfg.com/product/index.php?series=105,1
J11,USB SERVICE ONLY,1050170001,SimpleROV_HW:USB_MicroB_Molex105017_SilkTrim,,1
F1,500mA 32V FAST,0467.500NR,Fuse:Fuse_1206_3216Metric,,1
D1,SS14,SS14-E3/61T,Diode_SMD:D_SMA,,1
D2,SS14,SS14-E3/61T,SimpleROV_HW:D_SMA_SilkTrim,,1
D3,USBLC6-2SC6,USBLC6-2SC6,Package_TO_SOT_SMD:SOT-23-6,,1
D4,"BAT54S,215","BAT54S,215",Package_TO_SOT_SMD:SOT-23,,1
D5,STATUS GREEN,LTST-C190KGKT,LED_SMD:LED_0603_1608Metric,,1
Y1,12MHz CL10p,ABM8-272-T3,Crystal:Crystal_SMD_3225-4Pin_3.2x2.5mm,,1
SW1,BOOTSEL,B3U-1000P,Button_Switch_SMD:SW_SPST_B3U-1000P,,1
SW2,RESET,B3U-1000P,Button_Switch_SMD:SW_SPST_B3U-1000P,,1
R1,1k,RC0603FR-071KL,Resistor_SMD:R_0603_1608Metric,,1
R2,33,RC0603FR-0733RL,Resistor_SMD:R_0603_1608Metric,,1
R3,10k,RC0603FR-0710KL,Resistor_SMD:R_0603_1608Metric,,1
R4,1k,RC0603FR-071KL,Resistor_SMD:R_0603_1608Metric,,1
R5,10k,RC0603FR-0710KL,Resistor_SMD:R_0603_1608Metric,,1
R6,27,RC0603FR-0727RL,Resistor_SMD:R_0603_1608Metric,,1
R7,27,RC0603FR-0727RL,Resistor_SMD:R_0603_1608Metric,,1
R8,10,RC0603FR-0710RL,Resistor_SMD:R_0603_1608Metric,,1
R9,1k,RC0603FR-071KL,Resistor_SMD:R_0603_1608Metric,,1
R10,100k,RC0603FR-07100KL,Resistor_SMD:R_0603_1608Metric,,1
R11,2.2k,RC0603FR-072K2L,Resistor_SMD:R_0603_1608Metric,,1
R12,100k,RC0603FR-07100KL,Resistor_SMD:R_0603_1608Metric,,1
R13,100k,RC0603FR-07100KL,Resistor_SMD:R_0603_1608Metric,,1
R14,1k,RC0603FR-071KL,Resistor_SMD:R_0603_1608Metric,,1
R15,10k,RC0603FR-0710KL,Resistor_SMD:R_0603_1608Metric,,1
R16,100k,RC0603FR-07100KL,Resistor_SMD:R_0603_1608Metric,,1
R17,100k,RC0603FR-07100KL,Resistor_SMD:R_0603_1608Metric,,1
R18,365,RC0603FR-07365RL,Resistor_SMD:R_0603_1608Metric,,1
R22,100k,RC0603FR-07100KL,Resistor_SMD:R_0603_1608Metric,,1
R26,10k,RC0603FR-0710KL,Resistor_SMD:R_0603_1608Metric,,1
R30,100,RC0603FR-07100RL,Resistor_SMD:R_0603_1608Metric,,1
R19,365,RC0603FR-07365RL,Resistor_SMD:R_0603_1608Metric,,1
R23,100k,RC0603FR-07100KL,Resistor_SMD:R_0603_1608Metric,,1
R27,10k,RC0603FR-0710KL,Resistor_SMD:R_0603_1608Metric,,1
R31,100,RC0603FR-07100RL,Resistor_SMD:R_0603_1608Metric,,1
R20,365,RC0603FR-07365RL,Resistor_SMD:R_0603_1608Metric,,1
R24,100k,RC0603FR-07100KL,Resistor_SMD:R_0603_1608Metric,,1
R28,10k,RC0603FR-0710KL,Resistor_SMD:R_0603_1608Metric,,1
R32,100,RC0603FR-07100RL,Resistor_SMD:R_0603_1608Metric,,1
R21,365,RC0603FR-07365RL,Resistor_SMD:R_0603_1608Metric,,1
R25,100k,RC0603FR-07100KL,Resistor_SMD:R_0603_1608Metric,,1
R29,10k,RC0603FR-0710KL,Resistor_SMD:R_0603_1608Metric,,1
R33,100,RC0603FR-07100RL,Resistor_SMD:R_0603_1608Metric,,1
R34,33,RC0603FR-0733RL,Resistor_SMD:R_0603_1608Metric,,1
R35,33,RC0603FR-0733RL,Resistor_SMD:R_0603_1608Metric,,1
R36,4.7k,RC0603FR-074K7L,Resistor_SMD:R_0603_1608Metric,,1
R37,4.7k,RC0603FR-074K7L,Resistor_SMD:R_0603_1608Metric,,1
R38,10,RC0603FR-0710RL,Resistor_SMD:R_0603_1608Metric,,1
R39,100k,RC0603FR-07100KL,Resistor_SMD:R_0603_1608Metric,,1
R40,3.3k,RC0603FR-073K3L,Resistor_SMD:R_0603_1608Metric,,1
R41,3.3k,RC0603FR-073K3L,Resistor_SMD:R_0603_1608Metric,,1
R42,147k 0.1%,RT0603BRD07147KL,Resistor_SMD:R_0603_1608Metric,,1
R43,27k 0.1%,RT0603BRD0727KL,Resistor_SMD:R_0603_1608Metric,,1
R44,1k,RC0603FR-071KL,Resistor_SMD:R_0603_1608Metric,,1
R45,10k,RC0603FR-0710KL,Resistor_SMD:R_0603_1608Metric,,1
R46,100,RC0603FR-07100RL,Resistor_SMD:R_0603_1608Metric,,1
R47,100,RC0603FR-07100RL,Resistor_SMD:R_0603_1608Metric,,1
C1,4.7u 10V,GRM21BR71A475KA73L,Capacitor_SMD:C_0805_2012Metric,,1
C2,4.7u 10V,GRM21BR71A475KA73L,Capacitor_SMD:C_0805_2012Metric,,1
C3,100n 16V,GRM188R71C104KA01D,Capacitor_SMD:C_0603_1608Metric,,1
C4,1u 16V,GRM188R71C105KA12D,Capacitor_SMD:C_0603_1608Metric,,1
C5,2.2u 10V,GRM188R71A225KE15D,Capacitor_SMD:C_0603_1608Metric,,1
C6,100n 16V,GRM155R71C104KA88D,Capacitor_SMD:C_0402_1005Metric,,1
C7,100n 16V,GRM155R71C104KA88D,Capacitor_SMD:C_0402_1005Metric,,1
C8,100n 16V,GRM155R71C104KA88D,Capacitor_SMD:C_0402_1005Metric,,1
C9,100n 16V,GRM155R71C104KA88D,Capacitor_SMD:C_0402_1005Metric,,1
C10,100n 16V,GRM155R71C104KA88D,Capacitor_SMD:C_0402_1005Metric,,1
C11,100n 16V,GRM155R71C104KA88D,Capacitor_SMD:C_0402_1005Metric,,1
C12,100n 16V,GRM155R71C104KA88D,Capacitor_SMD:C_0402_1005Metric,,1
C13,100n 16V,GRM155R71C104KA88D,Capacitor_SMD:C_0402_1005Metric,,1
C14,1u 16V,GRM188R71C105KA12D,Capacitor_SMD:C_0603_1608Metric,,1
C15,100n 16V,GRM155R71C104KA88D,Capacitor_SMD:C_0402_1005Metric,,1
C16,15p 50V C0G,GRM1885C1H150JA01D,Capacitor_SMD:C_0603_1608Metric,,1
C17,15p 50V C0G,GRM1885C1H150JA01D,Capacitor_SMD:C_0603_1608Metric,,1
C18,2.2u 10V,GRM188R71A225KE15D,Capacitor_SMD:C_0603_1608Metric,,1
C19,100n 16V,GRM188R71C104KA01D,Capacitor_SMD:C_0603_1608Metric,,1
C20,10n 50V,GRM188R71H103KA01D,Capacitor_SMD:C_0603_1608Metric,,1
C21,100n 16V,GRM188R71C104KA01D,Capacitor_SMD:C_0603_1608Metric,,1
C22,100n 16V,GRM188R71C104KA01D,Capacitor_SMD:C_0603_1608Metric,,1
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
